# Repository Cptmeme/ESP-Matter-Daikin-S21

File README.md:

# Daikin S21 — Matter over Thread

> **⚠️ Disclaimer.** Opening your air conditioner exposes you to mains voltage and can damage the unit. Always disconnect mains power at the breaker before opening the indoor unit. Incorrect wiring on the S21 bus can damage the AC's controller board or the ESP32. You assume all responsibility for any damage, data loss, or device failure. This project is not affiliated with Daikin Industries, the Connectivity Standards Alliance, Espressif Systems, or RevK / the Faikin/Faikout project.

Open source Matter firmware for Daikin split air conditioners with an S21 port. Adds your AC to Apple Home, Google Home, Alexa, and Home Assistant — no Daikin app, no cloud, no BRP module. **Most modern Daikin split units have an S21 connector inside the indoor unit waiting to be used.**

> This release is the **Room Air Conditioner variant** — Matter device type `0x0072`, with **OnOff, Thermostat, Fan Control, and Temperature Measurement** clusters bundled into a single tile. Power, mode (Heat / Cool / Auto / Off), setpoint, current temperature, and fan speed all surface as native Matter attributes.
>
> **Powerful mode** is exposed on a second endpoint as an OnOff plug-in unit. In Apple Home and Google Home it appears as an "Outlet" tile next to the AC tile — rename it to "Powerful" in your home app.

> ⚠️ Uses ESP-Matter SDK test credentials (vendor `0xFFF1`, not VID/PID-certified). Functional for personal use; not suitable for resale as a certified Matter product.

---

## Contents

- [Quick Start](#quick-start)
- [Features](#features)
- [Compatible Hubs](#compatible-hubs)
- [Hardware](#hardware)
- [Pin configuration](#pin-configuration)
- [Building & Flashing](#building--flashing)
- [Commissioning](#commissioning)
- [Updating the Firmware](#updating-the-firmware)
- [Factory Reset](#factory-reset)
- [Known Issues / Roadmap](#known-issues--roadmap)
- [Customizing the device name](#customizing-the-device-name)
- [License](#license)
- [Matter and Thread Certification](#matter-and-thread-certification)
- [Contributing](#contributing)
- [Why?](#why)

---

## Quick Start

**You'll be building from source — there are no pre-built binaries (see [Building & Flashing](#building--flashing) for why).**

1. Install ESP-IDF and ESP-Matter — follow Espressif's [Getting the Repositories](https://docs.espressif.com/projects/esp-matter/en/latest/esp32/developing.html) guide.
2. Connect your interface board to the Daikin's S21 port — see [Hardware](#hardware).
3. Edit the GPIO pin defines in [`main/app_driver.cpp`](Thermostat_Daikin/main/app_driver.cpp) to match your wiring (see [Pin configuration](#pin-configuration)).
4. Build, flash, and monitor — see [Building & Flashing](#building--flashing).
5. [Commission](#commissioning) with your smart home app.

---

## Features

- ✅ Matter over Thread — uses the ESP32-C6's 802.15.4 radio, no WiFi required
- ✅ Compatible with Apple Home, Google Home, Alexa, Home Assistant, etc.
- ✅ Multi-fabric — commission to multiple hubs simultaneously
- ✅ Native Room Air Conditioner tile (single accessory in your home app)
- ✅ Power, Mode (Heat/Cool/Auto/Off), Setpoint, Current Temperature
- ✅ Fan speed (Low/Med/High/Auto + percent slider)
- ✅ Powerful mode as a separate switchable endpoint
- ✅ Live power draw (W) + lifetime energy (kWh) on S21 units that report it — surfaced via Matter Electrical Power/Energy Measurement clusters (Home Assistant displays them and can feed its Energy dashboard)
- ✅ Two-way state sync — adjusting on the Daikin remote updates your home app within ~2 seconds
- ✅ Factory reset via long press on the onboard button
- ✅ OTA-ready — dual OTA partitions with bootloader app-rollback for safe over-the-air updates (via a Matter OTA provider)

> **Fan speed visibility note:** Apple Home and Google Home (on IOS) currently *do not render* the fan slider on their AC tile, even when the firmware correctly advertises it. Home Assistant shows it. This is a controller-side UI limitation, not a firmware bug — the FanControl cluster is correctly registered and writable from any Matter controller that chooses to surface it.

---

## Compatible Hubs

> **Requires a Thread Border Router.** A Thread Border Router is required for any Matter-over-Thread device.

| Ecosystem | Tested |
|-----------|--------|
| Apple Home | ✅ (no fan speed control)*|
| Google Home | ✅ (no fan speed control on IOS)|
| Alexa | Untested |
| Home Assistant | ✅ |
| SmartThings | Untested |

>*Fan speed can be controlled through the Eve app or automations in the home app
---
### Hardware

**Recommended path: use a known-good interface board**

You need *something* between the ESP32-C6 and the Daikin's S21 port — the S21 bus is 5V logic and the ESP32 is 3.3V. A standard bidirectional level shifter (e.g. BSS138-based, like Adafruit / SparkFun "logic level converter" boards) works fine for the data lines if wired correctly; that's the same approach the included PCB uses. The reason for recommending a known-good board over breadboarding is more about getting the power supply, connectors, and protection right than about the level shifting being especially tricky.

> ⚠️ **Important — the included PCB inverts the S21 signals in hardware, and the firmware is written to match.** The bit-bang routines in `main/s21_driver.cpp` intentionally output and sample *inverted* logic levels (see `gpio_set_level(... bit ? 0 : 1)` at line 27 for TX and `if (level == 0) byte |= ...` at line 50 for RX). If you wire up a generic *non-inverting* level shifter, the AC will receive the wrong polarity and communication will silently fail. You then have two choices:
>
> - **Add a hardware inverter** in series with each S21 line (single transistor or a hex inverter IC like 74HC04), or
> - **Edit the firmware** to remove the inversion — flip the four `bit ? 0 : 1` / `parity ? 0 : 1` writes and the `level == 0` read in `main/s21_driver.cpp`.
>
> If you're using the included PCB, a Faikout, or any other interface that expects inverted-polarity drive, leave the firmware alone — it's already correct.

Two options that are known to work end-to-end:

1. **The reference PCB included in this repo** — see the `Custom PCB esp32c6/` folder. KiCad project + BOM. Built around an WT0132C6-S5, a BSS138 for level shifting, and a JST EH 5-way for the S21 connection. **Thread + Wi-Fi capable** thanks to the C6's 802.15.4 radio. *Note: This board does not feature an onboard USB port. Flashing is done via exposed `RX0` and `TX0` headers using an external USB-to-Serial adapter, and the board is powered via a wide-input `V_in` pin (accepting 4V to 36V).*
2. **A RevK ESP32-Faikout board.** This firmware's S21 implementation is derived from RevK's Faikout project and the Faikout hardware will work with it (you'll need to reflash with this firmware instead of Faikout's). 

If you want to roll your own interface, use the included PCB as a reference rather than starting from scratch.

> ⚠️ **Important — the included PCB inverts the S21 signals in hardware, and the firmware is written to match.** The bit-bang routines in [`main/s21_driver.cpp`](Thermostat_Daikin/main/s21_driver.cpp) intentionally output and sample *inverted* logic levels (see `gpio_set_level(... bit ? 0 : 1)` at line 27 for TX and `if (level == 0) byte |= ...` at line 50 for RX). If you wire up a generic *non-inverting* level shifter, the AC will receive the wrong polarity and communication will silently fail. You then have two choices:
>
> - **Add a hardware inverter** in series with each S21 line (single transistor or a hex inverter IC like 74HC04), or
> - **Edit the firmware** to remove the inversion — flip the four `bit ? 0 : 1` / `parity ? 0 : 1` writes and the `level == 0` read in [`main/s21_driver.cpp`](Thermostat_Daikin/main/s21_driver.cpp).
>
> If you're using the included PCB, a Faikout, or any other interface that expects inverted-polarity drive, leave the firmware alone — it's already correct.
>
> The included PCB is derived from RevK's [Faikout](https://codeberg.org/RevK/ESP32-Faikout) hardware, which is where the inverted-signal convention comes from. For the deeper "why" — schematic excerpts, component choices, and the historical context for why S21 interfaces are typically built this way — see RevK's repos on [Codeberg](https://codeberg.org/RevK).

Two options that are known to work end-to-end:

1. **The reference PCB included in this repo** — see the [`Custom PCB esp32c6/`](Custom%20PCB%20esp32c6/) folder. KiCad project + BOM.
2. **A RevK [ESP32-Faikout](https://codeberg.org/RevK/ESP32-Faikout) board.** This firmware's S21 implementation is derived from RevK's [Faikout]([https://codeberg.org/RevK/Faikin](https://codeberg.org/RevK/ESP32-Faikout)) project and the Faikout hardware will work with it (you'll need to reflash with this firmware instead of Faikout's). Faikout boards are sold by RevK and on Amazon UK — check the Faikout repo for current availability.

> **⚠️ Faikout = Matter over Wi-Fi only (for now).** Current Faikout PCBs use ESP32 / ESP32-S3 chips, neither of which has an 802.15.4 radio. That means **if you flash this firmware onto a Faikout board, you will be running Matter over Wi-Fi, not Thread** — no Thread Border Router involvement. The firmware supports both transports, so it'll commission and work fine; you just lose Thread's mesh / low-power benefits. A future Faikout revision based on the ESP32-C6 (or similar) would change this — track the Faikout repo if that matters to you.

If you want to roll your own interface, use the included PCB as a reference rather than starting from scratch.

### S21 connector pinout

Pinout, colors, and connector types are documented authoritatively in [Faikin's wiring wiki](https://codeberg.org/RevK/ESP32-Faikout/wiki/Wiring). Reproduced for convenience:

| Pin | Daikin color | Generic color | Function |
|-----|--------------|---------------|----------|
| 1 | Brown | Orange | 5V (not always connected; insufficient current for the board) |
| 2 | Red | Blue | TX from aircon (5V logic) |
| 3 | Orange | Yellow | RX to aircon (5V logic; most models accept 3.3V) |
| 4 | Yellow | Red | 12-14V (the actual power source — both Faikout and the included PCB run from this pin) |
| 5 | Blue | Black | GND |

> **Pin direction is from the aircon's perspective.** Pin 2 is the aircon's TX (data flowing *out* of the AC, *into* the ESP32). Pin 3 is the aircon's RX (data flowing *into* the AC, *from* the ESP32). The included PCB / Faikout handles the crossover correctly.

> **Power comes from pin 4, not pin 1.** Pin 1's 5V rail does not supply enough current to run the ESP32-C6 + interface logic. The included PCB uses a [TI TPS562246](https://www.ti.com/product/TPS562246) synchronous step-down (buck) converter to take the 12-14V from pin 4 down to 3.3V for the ESP32. Faikout uses a similar wide-input regulator and accepts anywhere from 4V to 36V on pin 4. **Do not try to power the board from pin 1.**

**Two physical connector variants exist on the Daikin side:**
- **Type A** — JST EH (2.5 mm pitch), older models
- **Type B** — JST PAP (2.0 mm pitch), newer models

The boards above use JST EH male (5-way). For Type B units you need either a Type-A-to-Type-B cable or a different connector on the board. Faikin's wiring wiki links to per-type cable drawings.

### Where to find the S21 port on your AC

- [Faikin's confirmed-working models list](https://codeberg.org/RevK/ESP32-Faikout/wiki/List-of-confirmed-working-air-con-units) — start here. If your model is on this list it has S21.
- [Faikin's FTXM wiring teardown](https://codeberg.org/RevK/ESP32-Faikout/wiki/FTXMxxW2VMA-Wiring) — step-by-step photos for the FTXM series, the most common Daikin split.
- For other models the S21 port is generally on the indoor unit's main controller PCB, accessible after removing the front cover and electrical-bay cover.

### ESP32-C6 GPIO assignments (firmware side)

| ESP32-C6 GPIO | Function |
|---------------|----------|
| GPIO 20 | S21 RX (input) — receives data from the AC |
| GPIO 21 | S21 TX (output) — transmits to the AC |
| GPIO 23 | Factory-reset / commissioning button → GND (active low, internal pull-up) |

> **GPIO TX/RX naming is from the ESP32's perspective.** GPIO21 is an output, GPIO20 is an input. This is the opposite of the S21 connector's pin labels (which are from the AC's perspective). The included PCB and Faikout both wire the crossover correctly — you don't need to think about it if you're using either board.

### Factory-reset button

A long press on the GPIO23 button triggers a Matter factory reset (clears all fabrics and re-enters BLE commissioning mode). A short press opens a new commissioning window if no fabric is paired.

---

## Pin configuration

Unless your hardware matches the [included PCB](Custom%20PCB%20esp32c6/) exactly, you'll need to change the GPIO pin assignments to match your wiring before building. They're defined as preprocessor macros at the top of [`main/app_driver.cpp`](Thermostat_Daikin/main/app_driver.cpp):

```c
#define S21_TX_PIN       21   // ESP32 → S21 RX  (output)
#define S21_RX_PIN       20   // ESP32 ← S21 TX  (input)
#define BUTTON_GPIO_PIN  23   // factory-reset / commissioning button → GND
```

Pick GPIOs that are safe to use as general-purpose IO on your specific ESP32 variant (avoid strapping pins, JTAG pins, USB pins, etc.). For ESP32-C6 the [Espressif datasheet pinout table](https://www.espressif.com/sites/default/files/documentation/esp32-c6_datasheet_en.pdf) is the authoritative reference.

If you're using a board where the buttons or LEDs are on different pins than the included PCB, you may also need to adjust them in `app_driver.cpp` and `app_main.cpp`.

---

## Building & Flashing

> **Why no pre-built binaries?** This firmware needs the GPIO pin assignments compiled in (see above). Unless you're using the exact PCB in this repo, the pre-built binary would have wrong pins for your wiring and either silently fail to talk to the AC or behave unpredictably. So you build from source.

### Hardware setup for flashing

Because the included PCB does not have an onboard USB port, you will need a USB-to-Serial (UART) adapter (like an FTDI or CH340 board) to flash the ESP32-C6.

> ⚠️ **CRITICAL: 3.3V Logic vs. 5V Power**
> The ESP32-C6 requires **3.3V logic** on its `RX0` and `TX0` pins. Applying 5V data signals will permanently damage the chip. However, the board itself must be powered with at least 4V via the `V_in` pin so the onboard step-down converter can function.
> 
> **You must use a UART adapter set to 3.3V logic, but use a 5V pin for power.** Many standard FTDI adapters have a jumper or switch to set the TX/RX logic levels to 3.3V while still exposing a dedicated 5V VCC pin. Do not use a 3.3V power source for `V_in`.

**Wiring your UART adapter:**
* **TX** on adapter (3.3V logic) ➔ **RX0** on PCB
* **RX** on adapter (3.3V logic) ➔ **TX0** on PCB
* **GND** on adapter ➔ **GND** on PCB
* **5V** on adapter (Power) ➔ **V_in** on PCB 

Make sure to put your ESP32-C6 into **Download Mode** before flashing (typically by holding the BOOT button/pin low while pulling the EN Reset pin low, then releasing EN, then releasing BOOT).

### 1. Install ESP-IDF and ESP-Matter

Follow Espressif's official setup: **[Getting the ESP-Matter Repositories](https://docs.espressif.com/projects/esp-matter/en/latest/esp32/developing.html)**. The short version on macOS / Linux:

```bash
mkdir -p ~/esp && cd ~/esp
git clone -b v5.4.1 --recursive https://github.com/espressif/esp-idf.git
cd esp-idf && ./install.sh esp32c6 && cd ..
git clone -b release/v1.5 --depth 1 https://github.com/espressif/esp-matter.git
cd esp-matter && ./install.sh && cd ..
```

**Versions.** This firmware is built against **ESP-Matter v1.5**. Its clean, officially-supported pairing is **ESP-IDF v5.4.1** — with that combo the build "just works" apart from the optional cosmetic patch below. **ESP-IDF v5.5.x also builds, but requires the first SDK patch below** (its `@`-response-file compiler flags otherwise break connectedhomeip's GN argument generation).

### 1a. Apply the ESP-Matter SDK patch

A small fix is needed **in the ESP-Matter SDK itself** — it lives under `~/esp/esp-matter/…`, *outside this repo*, so apply it after cloning esp-matter (and re-apply if you ever update or re-install esp-matter):

**Patch — GN build fix (required on ESP-IDF 5.5.x; not needed on 5.4.1).**
Without it, the build aborts with `ERROR at build arg file … Invalid token`. IDF 5.5 puts flags such as `-march` into a GCC `@response-file`, and connectedhomeip's `create_args_gn.py` wraps the whole `@"…"` token in quotes, which GN can't parse. Edit
`connectedhomeip/connectedhomeip/config/esp32/components/chip/create_args_gn.py` — immediately after the line `compile_flags = compile_command.split()[1:-4]`, expand any `@`-file back into real flags:

```python
expanded = []
for f in compile_flags:
    if f.startswith('@'):
        try:
            with open(f[1:].strip('"')) as rsp:
                expanded.extend(rsp.read().split())
            continue
        except OSError:
            pass
    expanded.append(f)
compile_flags = expanded
```

Then force a regen of the CHIP build: `rm -rf build/esp-idf/chip` and rebuild.

### 2. Configure your environment in every new shell

```bash
source ~/esp/esp-idf/export.sh
source ~/esp/esp-matter/export.sh
```

### 3. Build and flash

```bash
git clone https://github.com/cptmeme/ESP-Matter-Daikin-S21.git
cd ESP-Matter-Daikin-S21/Thermostat_Daikin

# Edit main/app_driver.cpp first if your pins differ from the included PCB.

idf.py set-target esp32c6
idf.py build
idf.py -p <PORT> flash monitor
```

Replace `<PORT>` with your serial port (`/dev/cu.usbserial-XXXX` on macOS, `/dev/ttyUSB0` on Linux, `COM3` on Windows).

> ⚠️ **Disconnect mains power at the breaker before opening the indoor unit.** The S21 port itself is logic-level and isolated from mains, but everything around it inside the cabinet is not. If you're not comfortable working inside an AC indoor unit, have a qualified technician install the cable for you and just plug into the S21 connector once it's accessible.

### 4. Verify the firmware is running

In the `idf.py monitor` output, after the boot banner you should see:

```
I (xxxx) app_main: Room Air Conditioner created with endpoint_id 1
I (xxxx) app_main: Powerful plug-in unit created with endpoint_id 2
I (xxxx) app_main: Commissioning window opened
```

This confirms Matter is initialized and the device is advertising for commissioning over BLE.

## Commissioning

- Commission devices ONE AT A TIME.
- Power off or move away other un-commissioned devices while setting up each one.
- All devices share the same pairing code, so the controller may get confused if multiple are advertising simultaneously.
- Once commissioned, each device gets a unique identity on your network.

### Apple Home

1. Open the **Home** app.
2. Tap **+** → **Add Accessory**.
3. Tap **More Options** to enter the setup code manually.
4. Press **Add Anyway** when prompted (this is expected — see [Matter and Thread Certification](#matter-and-thread-certification)).
5. Name the device and place it in a room. You'll see two tiles: the AC and the "Outlet" (Powerful). Rename the Outlet to "Powerful" or similar.

```
Setup code: 3497-011-2332
```

> ⚠️ This is the ESP-Matter SDK test setup code, used by all devices running this firmware. Once a device is commissioned to your Matter fabric, the setup code is no longer used for authentication — your Matter ecosystem manages credentials going forward. Multiple uncommissioned devices broadcasting the same setup code is why the commissioning instructions specify one device at a time.

> **Apple Home creates two fabrics during pairing.** This is normal. Apple Inc. (vendor `0x1349`) is the local Home Hub admin; Apple Keychain (vendor `0x1384`) is Apple's iCloud-based admin that lets all your Apple devices control the unit. Both fabrics are Apple's — you have not been auto-shared with a third party.

<details>
<summary>Google Home / Alexa / Home Assistant commissioning</summary>

Google Home, Alexa, and Home Assistant all support Matter commissioning via their respective apps and integrations. Use setup code `3497-011-2332` or the QR code above when prompted.

**Home Assistant specifically renders the fan slider** for this device, which Apple Home currently omits on their AC tile.

</details>

---

## Updating the Firmware

### Versions

Bump all three for every release, or the device ignores the update. The build fails if the two numbers differ.

* `PROJECT_VER` (e.g. `"1.1"`) and `PROJECT_VER_NUMBER` (e.g. `2`) in `Thermostat_Daikin/CMakeLists.txt`
* `CONFIG_DEVICE_SOFTWARE_VERSION_NUMBER` in `Thermostat_Daikin/sdkconfig` / `sdkconfig.defaults.esp32c6` (same number)

### Over serial

A normal `idf.py -p <PORT> flash` over the UART adapter still works (see [Hardware setup for flashing](#hardware-setup-for-flashing)).

### Over the air (Matter OTA over Thread)

The build also produces `build/thermostat-ota.bin`, a Matter OTA image. Apple Home and Google Home only update certified devices, so you serve it yourself with the Matter SDK's host tools. Build them from the SDK with `./scripts/build/build_examples.py --target darwin-arm64-chip-tool --target darwin-arm64-ota-provider build`.

One-time setup: in the Home app, turn on pairing mode for the AC, then add the provider and the AC to `chip-tool`'s fabric:

```bash
chip-tool pairing code 2 <setup-code-from-home-app>              # AC = node 2
chip-ota-provider-app -f build/thermostat-ota.bin --discriminator 3841 --secured-device-port 5565 &
chip-tool pairing onnetwork-long 1 20202021 3841                 # provider = node 1
chip-tool accesscontrol write acl '[{"fabricIndex": 1, "privilege": 5, "authMode": 2, "subjects": [112233], "targets": null}, {"fabricIndex": 1, "privilege": 3, "authMode": 2, "subjects": null, "targets": [{"cluster": 41, "endpoint": null, "deviceType": null}]}]' 1 0
```

Each update (with the provider running and serving the new `thermostat-ota.bin`):

```bash
chip-tool otasoftwareupdaterequestor announce-otaprovider 1 0 2 0 2 0
chip-tool basicinformation read software-version 2 0              # afterwards: the new number
```

The 1.75 MB image takes about a quarter of an hour over Thread. The AC then restarts into the new version and keeps it once it has run for a minute while attached to the Thread network. If it doesn't get there within 5 minutes, or crashes before that, the bootloader automatically returns to the previous version.

Rollback needs a bootloader built with rollback enabled (this build, and earlier builds since energy monitoring was added), and the bootloader can only be written over serial. A device with an older bootloader still updates fine over the air, it just won't roll back.

---

## Factory Reset

Hold the onboard reset button (GPIO23 → GND) for **several seconds**. The device will clear all fabrics and re-enter BLE commissioning mode. Make sure to also remove the device from whatever ecosystems you've added it to — controllers cache credentials and will refuse re-pairing otherwise.

---

## Known Issues / Roadmap
- [x] **Energy reporting** — live power (W) + lifetime imported energy (kWh) via the Matter Electrical Power/Energy Measurement clusters, on S21 units that report it. Home Assistant shows both; the cooling/heating split is read but only logged (Matter carries a single imported/exported energy value, not a per-mode breakdown).
- [ ] **Swing / louver position** — the S21 protocol supports it; no Matter wiring yet.
- [x] **X50A & CN_WIRED protocols (experimental)** — drivers for both are built in, with boot-time auto-detection (S21 → X50A → CN_WIRED). **Only S21 is hardware-verified.** X50A rides the same 2-wire UART front-end and should work with the right cable; CN_WIRED is a single-wire pulse protocol that needs a different connector/pull-up. Toggle them via `AC_ENABLE_X50A` / `AC_ENABLE_CNWIRED` in `Thermostat_Daikin/main/app_driver.cpp`.

---

## Customizing the device name

To change the manufacturer / model / default name shown in your home app, edit [`main/CHIPProjectConfig.h`](Thermostat_Daikin/main/CHIPProjectConfig.h) before building:

```c
#define CHIP_DEVICE_CONFIG_DEVICE_VENDOR_NAME   "Daikin"
#define CHIP_DEVICE_CONFIG_DEVICE_PRODUCT_NAME  "Daikin A/C"
#define CHIP_DEVICE_CONFIG_DEFAULT_NODE_LABEL   "Daikin Thermostat"
```

Apple Home, Google Home, and Alexa display these in the device's settings page. Changing them after the device is already commissioned won't update existing controllers — you'll need to factory reset and re-commission.

---

## License

GPL v3 — see [LICENSE](LICENSE)

The S21 protocol implementation is derived from the [Faikout](https://codeberg.org/RevK/ESP32-Faikout) project by RevK, which is licensed under GPL v3 — that's why this firmware is also GPL v3. Combined with portions of the [ESP-Matter](https://github.com/espressif/esp-matter) thermostat example by Espressif Systems (Apache 2.0, which is GPL-compatible in this direction).

---

## Matter and Thread Certification

This firmware is **not** Matter Certified or Thread Certified. It implements the Matter protocol via Espressif's [esp-matter](https://github.com/espressif/esp-matter) SDK and Thread via OpenThread, but has not been submitted to the Connectivity Standards Alliance (CSA) or Thread Group for certification. Certification requires CSA membership ($7,000+/year) and Authorized Test Lab evaluation, which are out of scope for an open-source community project.

Devices flashed with this firmware will appear in Matter ecosystems as **uncertified Matter devices**. Most ecosystems show a one-time warning during commissioning ("Add Anyway" in Apple Home); this is normal and expected.

This firmware uses the publicly available ESP-Matter test VID/PID and setup code, which is acceptable for personal use and development but cannot be used in commercial certified products.

"Matter" is a trademark of the Connectivity Standards Alliance. "Thread" is a trademark of the Thread Group. "Daikin" is a trademark of Daikin Industries, Ltd. This project is not affiliated with, endorsed by, or sponsored by any of these organizations.

---

## Contributing

Contributions are welcome. This is a solo-maintained project, so response times will vary, but every issue and PR gets read.

### Reporting bugs

Open a [GitHub issue](../../issues/new) with:

- **Hardware:** ESP32-C6 board variant, S21 interface design (optocoupler / FET / which PCB), and Daikin model number
- **Ecosystem:** Apple Home, Google Home, Alexa, Home Assistant, etc., and the Thread Border Router(s) on your network
- **What happened:** What you expected, what actually occurred, and steps to reproduce
- **Logs:** Serial monitor output at 115200 baud, especially anything around the failure point

If your device commissions but the AC never updates state, the most likely cause is the S21 interface — wrong wiring, wrong connector type (Type A vs B), or the wrong GPIO pins compiled in (check [`main/app_driver.cpp`](Thermostat_Daikin/main/app_driver.cpp)). Verify by trying with the [included PCB](Custom%20PCB%20esp32c6/) or a [Faikout](https://codeberg.org/RevK/ESP32-Faikout) board, both of which are known-good.

---

## Why?

Daikin makes excellent air conditioners and a famously poor cloud experience. The official path to remote control is the BRP-series WiFi adapter and the Daikin app, which:

- Costs €100+ for a module that's a glorified ESP32 + their cloud
- Routes every command through Daikin's servers
- Has no native Matter, HomeKit, or local API
- Stops working the moment Daikin retires the cloud product
- Doesn't extend to multiple ecosystems — it's the Daikin app or nothing

Meanwhile, most modern Daikin split units ship with an **S21 service port** sitting unused inside the indoor unit, exposing the full feature set of the AC over a documented(-ish) serial protocol. RevK's [Faikout](https://codeberg.org/RevK/ESP32-Faikout) project did the hard work of reverse-engineering the protocol and shipping the [Faikout](https://codeberg.org/RevK/ESP32-Faikout) hardware. This project bolts a Matter front-end onto that work — turning the same hardware into a fully local, cloud-free, multi-ecosystem Matter accessory that works directly with Apple Home, Google Home, Alexa, and Home Assistant. No app to install, no servers to depend on, no recurring fee.

### Why Matter over Thread?

Matter over Thread offers lower power consumption, lower latency, and a mesh that doesn't depend on your WiFi. Thread devices use any compatible Thread Border Router (HomePod mini, Apple TV 4K, iPhone 15 Pro+, Nest Hub 2nd gen, HA SkyConnect/Yellow) and continue to function even if your WiFi is down or congested. The ESP32-C6 has both a WiFi 6 radio and an 802.15.4 Thread radio — this firmware uses the Thread radio so the WiFi stack can stay quiet.

### Why Matter, and not Faikin / ESPHome / Tasmota?

Faikin is excellent and deserves credit — it's the source of this project's S21 implementation and the entire reason the protocol is documented at all. But Faikin (and ESPHome, Tasmota) all assume a central controller: Home Assistant, an MQTT broker, or a custom dashboard. They're great if that's your setup. They're a problem if it isn't.

This firmware speaks Matter directly. There's no middleware:

- **Apple Home user without Home Assistant?** It just works. Commission directly from the Home app.
- **Google Home or Alexa user?** Same — direct Matter commissioning, no third-party hub.
- **Home Assistant user?** Also works — commission via HA's Matter integration. Bonus: HA renders the fan slider that Apple omits.
- **Multi-ecosystem household?** Multi-fabric commissioning lets the same device live in Apple Home, HA, and Google Home simultaneously.

Matter is an industry-standard protocol — your AC works with the ecosystems you have today and remains compatible with new Matter ecosystems as they appear.

---

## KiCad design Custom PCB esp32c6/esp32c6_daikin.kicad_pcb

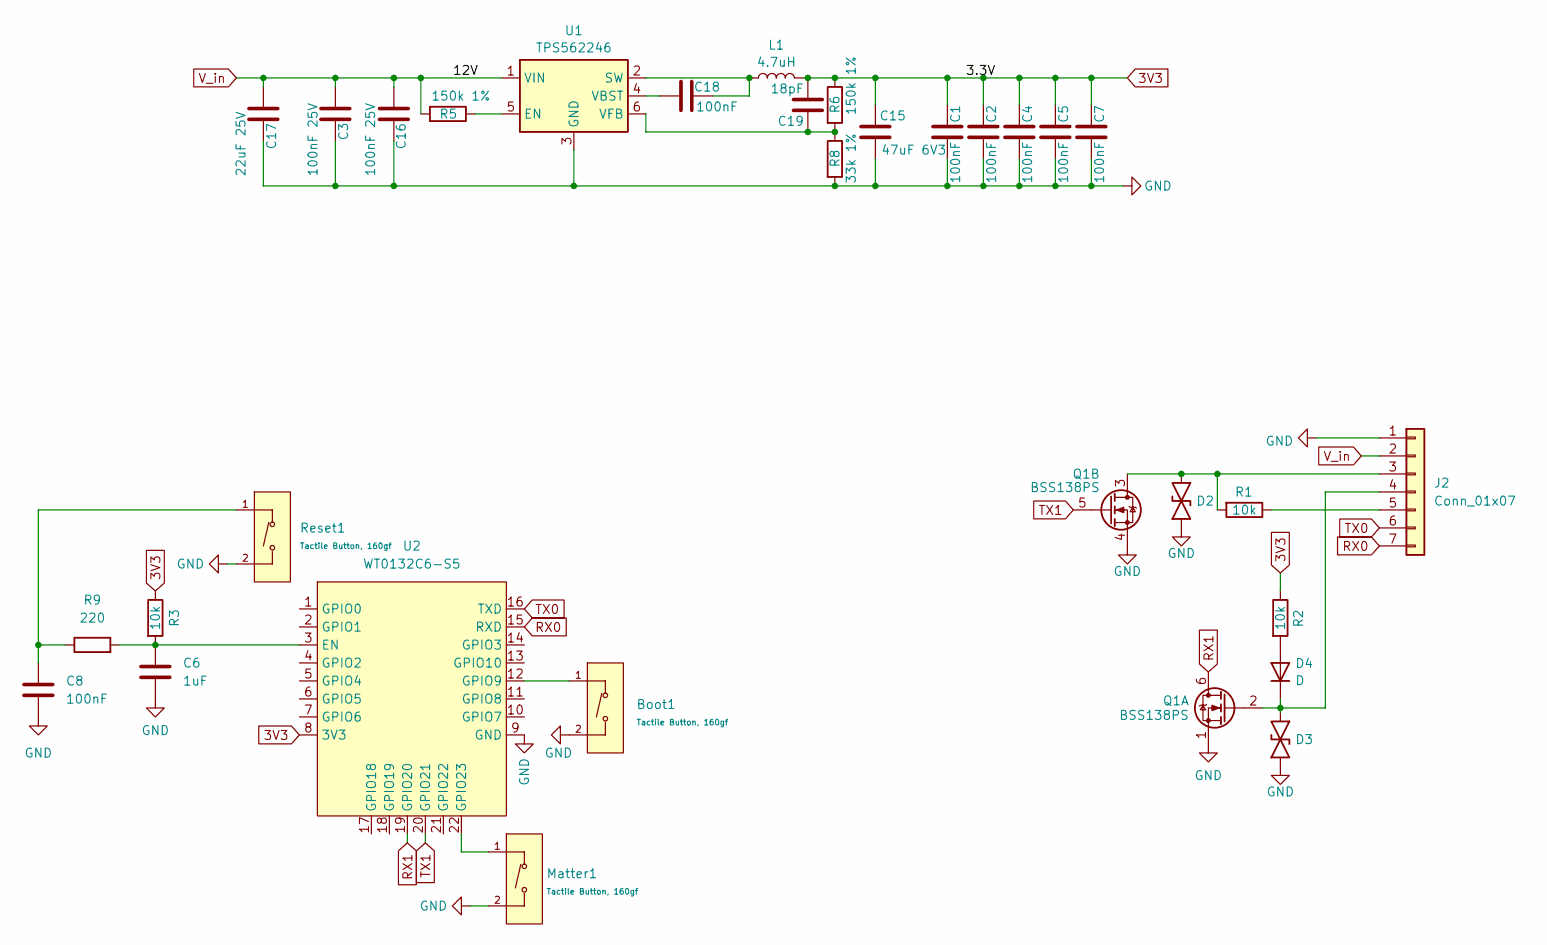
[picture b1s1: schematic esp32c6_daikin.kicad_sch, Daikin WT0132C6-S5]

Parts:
Boot1: Tactile Button, 160gf; SW-SMD_L3.9-W3.0-P4.45; Voltage Rating (Dc) 12V; Part TS-1088-AR02016; LCSC C720477
C1, C2, C4, C5, C7, C8, C18: 100nF; C0402; LCSC C1525
C3, C16: 100nF 25V; C0402; LCSC C307331
C6: 1uF; C0603; LCSC C15849
C15: 47uF 6V3; C0805; LCSC C16780
C17: 22uF 25V; C0805; LCSC C45783
C19: 18pF; C0402; LCSC C1549
D2, D3: DFN1006-2L_L1.0-W0.6-P0.65-BI; MPN C5137770
D4: D; D0402; MPN C28642302
J2: Conn_01x07; PinHeader_1x07_P2.54mm_Horizontal
L1: 4.7uH; IND-SMD_L4.9-W4.9_NRS50XX; LCSC C307876
Matter1: Tactile Button, 160gf; SW-SMD_L3.9-W3.0-P4.45; Voltage Rating (Dc) 12V; Part TS-1088-AR02016; LCSC C720477
Q1: BSS138PS; SOT-363_L2.0-W1.3-P0.65-LS2.1-BR; MPN C193381
R1, R2: 10k; R0402; MPN C25744
R3: 10k; R0402; LCSC C25744
R5, R6: 150k 1%; R0603; LCSC C22807
R8: 33k 1%; R0402; LCSC C25779
R9: 220; R0402; LCSC C25091
Reset1: Tactile Button, 160gf; SW-SMD_L3.9-W3.0-P4.45; Voltage Rating (Dc) 12V; Part TS-1088-AR02016; LCSC C720477
U1: TPS562246; SOT-5X3-6_L1.6-W1.2-P0.50-LS1.6-BR; LCSC C41833479
U2: WT0132C6-S5; LCSC Part C9900241604

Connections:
3V3: C1.2, C2.2, C4.2, C5.2, C7.2, C15.1, C19.2, L1.2, R2.1, R3.1, R6.1, U2.8 (3V3)
GND: Boot1.2 (B), C1.1, C2.1, C3.2, C4.1, C5.1, C6.2, C7.1, C8.2, C15.2, C16.2, C17.2, D2.1, D3.1, J2.1, Matter1.2 (B), Q1.1 (SN), Q1.4 (DP), R8.2, Reset1.2 (B), U1.3 (GND), U2.9 (GND)
unnamed: Boot1.1 (A), U2.12 (GPIO9)
unnamed: D4.2 (A), R2.2
unnamed: D3.2, D4.1 (K), J2.4, Q1.2 (GN)
unnamed: D2.2, J2.3, Q1.3 (SP), R1.2
unnamed: J2.5, R1.1
unnamed: Matter1.1 (A), U2.22 (GPIO23)
unnamed: C8.1, R9.1, Reset1.1 (A)
unnamed: R5.1, U1.5 (EN)
unnamed: C18.2, L1.1, U1.2 (SW)
unnamed: C18.1, U1.4 (VBST)
unnamed: C19.1, R6.2, R8.1, U1.6 (VFB)
unnamed: C6.1, R3.2, R9.2, U2.3 (EN)
RX0: J2.7, U2.15 (RXD)
RX1: Q1.6 (DN), U2.19 (GPIO20)
TX0: J2.6, U2.16 (TXD)
TX1: Q1.5 (GP), U2.20 (GPIO21)
V_in: C3.1, C16.1, C17.1, J2.2, R5.2, U1.1 (VIN)

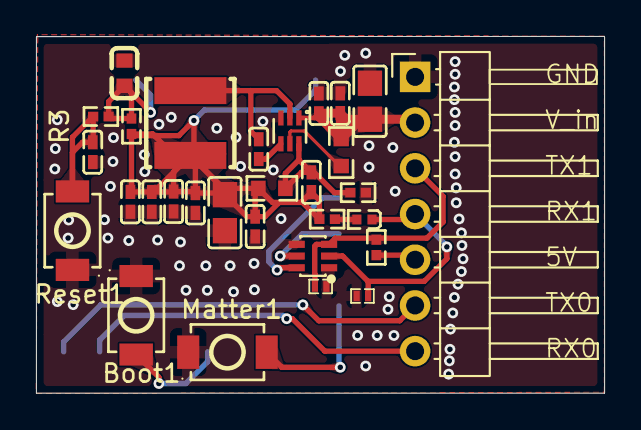
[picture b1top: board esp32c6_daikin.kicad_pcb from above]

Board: 2 copper layers, 31.6 x 19.8 mm, 31 parts (1 on the bottom side), 19 nets.

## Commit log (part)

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2026-01-09 Correct link for ESP32-Faikout in README
    Updated references for the ESP32-Faikout project in the README.
2026-02-22 fix not turning off through automations
2026-02-22 Fix: not turning off through automations
2026-02-22 Enhance README with new features and fixes
    Updated README to reflect support for auto mode and powerful feature.
2026-02-22 add powerful mode
    Support for powerful mode as an extra switch
2026-02-22 Update README with powerful mode support
    Updated README to reflect new powerful mode support and removed outdated bug note.
2026-03-12 Create LICENSE
2026-05-10 change device name
2026-05-10 change name/version v2
2026-05-10 Change from thermostat cluster to room ac
2026-05-10 Update README.md
    Removed release and downloads badges from README.
2026-05-10 Update README to clarify Quiet mode exposure
    Removed note about Quiet mode not being exposed due to Matter limitations.
2026-05-10 Rename README_old.md to README.md
2026-05-10 Revise Thread Border Router compatibility table
    Updated the compatibility table for Thread Border Routers to improve clarity and organization.
2026-05-10 Update README with fan speed control information
    Added note about fan speed control through the Eve app.
2026-05-10 Fix formatting issue in README.md
2026-06-30 Update SmartThings compatibility status in README
